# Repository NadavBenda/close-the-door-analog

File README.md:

# Close-the-Door Analog Reminder 🚪🔊

A small battery-powered analog reminder circuit for a shared-house door.

If the door is left open for more than a short delay, the circuit emits a gentle beep sequence as a reminder to close it. The design is intentionally implemented without a microcontroller, using discrete analog/timing logic.

## Motivation

This project started from a real everyday problem: people passing through a shared hallway door often leave it open. Instead of using a software-heavy smart-home solution, the goal was to build a small, manufacturable analog PCB and practice the full hardware design flow independently.

## Design Goals

* Fully analog / no MCU
* Battery powered
* Low standby current
* Reed-switch door sensing
* Gentle, non-intrusive acoustic reminder
* Simple PCB suitable for low-cost fabrication and assembly
* Designed as a first independent end-to-end PCB project

## System Overview

The circuit consists of:

* Reed switch for door-state detection
* CMOS timer logic for delay and beep timing
* Logic gates for signal conditioning
* Passive piezo transducer for the sound output
* Coin-cell battery supply
* Test points for bring-up and debugging

Basic behavior:

```text
Door opens
→ delay timer starts
→ if condition is met
→ short beep sequence
→ silence
```

## Hardware

The board was designed in KiCad and sent to fabrication through JLCPCB.

Main design considerations included:

* Low standby current
* Mechanical placement of reed switch and magnet
* Decoupling for CMOS timing ICs
* Passive piezo drive
* Testability during bring-up
* Manufacturable footprints and BOM preparation

## Status

Assembled

## Known Limitations 

Capacitor Discharge Time: Because the timing circuit is purely analog, the timing capacitor requires a brief period to discharge fully after the door is closed. If the door is cycled (opened and closed) in very rapid succession, the capacitor may remain partially charged, causing the subsequent alarm delay to trigger sooner than the configured duration.

## License

This project is shared for learning and reference

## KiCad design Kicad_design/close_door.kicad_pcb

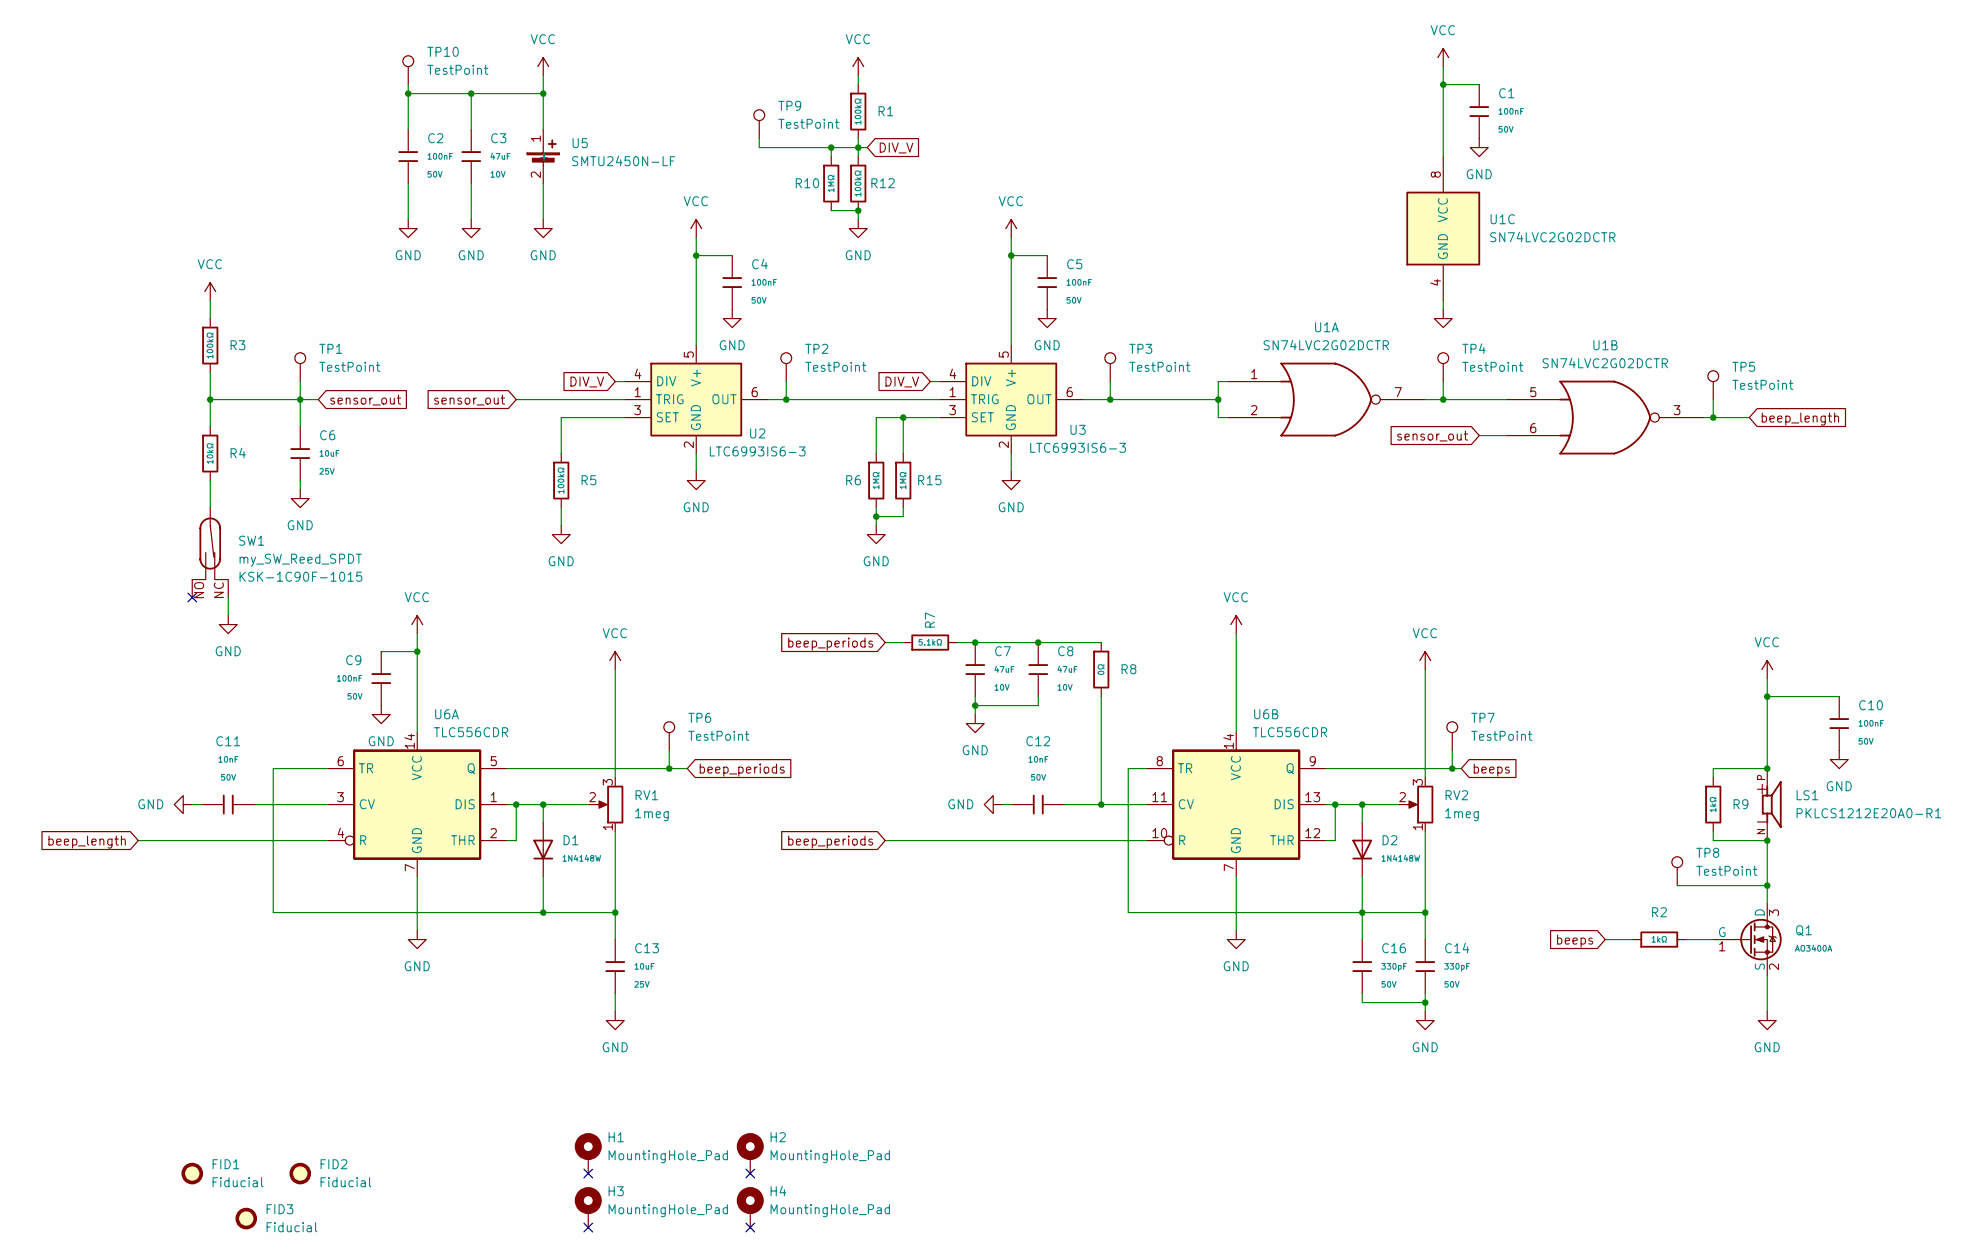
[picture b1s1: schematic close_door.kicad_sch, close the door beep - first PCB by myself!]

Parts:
C1, C2, C4, C5, C9, C10: 100nF; C_0805_2012Metric; Voltage Rated 50V; Tolerance ±10%; Part CC0805KRX7R9BB104; LCSC C49678
C3, C7, C8: 47uF; C_1206_3216Metric; Voltage Rated 10V; Tolerance ±20%; Part CL31A476MPHNNNE; LCSC C96123
C6, C13: 10uF; C_0805_2012Metric; Voltage Rated 25V; Tolerance ±10%; Part CL21A106KAYNNNE; LCSC C15850
C11, C12: 10nF; C_0805_2012Metric; Voltage Rated 50V; Tolerance ±10%; Part CL21B103KBANNNC; LCSC C1710
C14, C16: 330pF; C_0603_1608Metric; Voltage Rated 50V; Tolerance ±5%; Part CL10C331JB8NNNC; LCSC C1664
D1, D2: 1N4148W; D_SOD-123; Forward Voltage (Vf@If) 1V@50mA; Reverse Voltage (Vr) 75V; Part 1N4148W; LCSC C81598
FID1, FID2, FID3: Fiducial; Fiducial_1mm_Mask2mm_with_keepout
H1, H2, H3, H4: MountingHole_Pad; MountingHole_3.2mm_M3_Pad
LS1: PKLCS1212E20A0-R1; PARTREV January 22, 2018
Q1: AO3400A; SOT-23; Part AO3400A; LCSC C20917
R1, R3, R5, R12: 100kΩ; R_0805_2012Metric; Overload Voltage (Max) 150V; Tolerance ±1%; Part 0805W8F1003T5E; LCSC C149504
R2, R9: 1kΩ; R_0805_2012Metric; Overload Voltage (Max) 150V; Tolerance ±1%; Part 0805W8F1001T5E; LCSC C17513
R4: 10kΩ; R_0805_2012Metric; Overload Voltage (Max) 150V; Tolerance ±1%; Part 0805W8F1002T5E; LCSC C17414
R6, R10, R15: 1MΩ; R_0805_2012Metric; Overload Voltage (Max) 150V; Tolerance ±1%; Part 0805W8F1004T5E; LCSC C17514
R7: 5.1kΩ; R_0805_2012Metric; Overload Voltage (Max) 150V; Tolerance ±1%; Part 0805W8F5101T5E; LCSC C27834
R8: 0Ω; R_0805_2012Metric; Overload Voltage (Max) 150V; Tolerance ±1%; Part 0805W8F0000T5E; LCSC C17477
RV1, RV2: 1meg; Potentiometer_Bourns_3296W_Vertical; MPN 3296W-1-105LF; LCSC C83687
SW1: my_SW_Reed_SPDT; KSK-1C90F-1015; MPN KSK-1C90F-1015
TP1, TP2, TP3, TP4, TP5, TP6, TP7, TP8, TP9, TP10: TestPoint; TestPoint_Pad_D1.5mm
U1: SN74LVC2G02DCTR; SOP65P400X130-8N; MPN SN74LVC2G02DCTR; LCSC C94600
U2, U3: LTC6993IS6-3; TSOT-23-6; MPN LTC6993IS6-3#TRMPBF
U5: SMTU2450N-LF; SMTU2450N1LF; Mouser Part Number 614-SMTU2450N-LF.TR
U6: TLC556CDR; SOIC-14_3.9x8.7mm_P1.27mm; MPN TLC556CDR; LCSC C201587

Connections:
DIV_V: R1.2, R10.1, R12.1, TP9.1, U2.4 (DIV), U3.4 (DIV)
GND: C1.2, C2.2, C3.2, C4.2, C5.2, C6.2, C7.2, C8.2, C9.2, C10.2, C11.1, C12.1, C13.2, C14.2, C16.2, Q1.2 (S), R5.2, R6.2, R10.2, R12.2, R15.2, SW1.1, U1.4 (GND), U2.2 (GND), U3.2 (GND), U5.2 (-), U6.7 (GND)
unnamed: C7.1, C8.1, R7.2, R8.1
unnamed: LS1.N, Q1.3 (D), R9.2, TP8.1
unnamed: Q1.1 (G), R2.2
unnamed: R4.2, SW1.2
unnamed: TP4.1, U1.5, U1.7
unnamed: TP2.1, U2.6 (OUT), U3.1 (TRIG)
unnamed: R5.1, U2.3 (SET)
unnamed: TP3.1, U1.1, U1.2, U3.6 (OUT)
unnamed: R6.1, R15.1, U3.3 (SET)
unnamed: C11.2, U6.3 (CV)
unnamed: D1.2, RV1.2, U6.1 (DIS), U6.2 (THR)
unnamed: C13.1, D1.1, RV1.1, U6.6 (TR)
unnamed: C12.2, R8.2, U6.11 (CV)
unnamed: D2.2, RV2.2, U6.12 (THR), U6.13 (DIS)
unnamed: C14.1, C16.1, D2.1, RV2.1, U6.8 (TR)
VCC: C1.1, C2.1, C3.1, C4.1, C5.1, C9.1, C10.1, LS1.P, R1.1, R3.1, R9.1, RV1.3, RV2.3, TP10.1, U1.8 (VCC), U2.5 (V+), U3.5 (V+), U5.1 (+), U6.14 (VCC)
beep_length: TP5.1, U1.3, U6.4 (R)
beep_periods: R7.1, TP6.1, U6.5 (Q), U6.10 (R)
beeps: R2.1, TP7.1, U6.9 (Q)
sensor_out: C6.1, R3.2, R4.1, TP1.1, U1.6, U2.1 (TRIG)

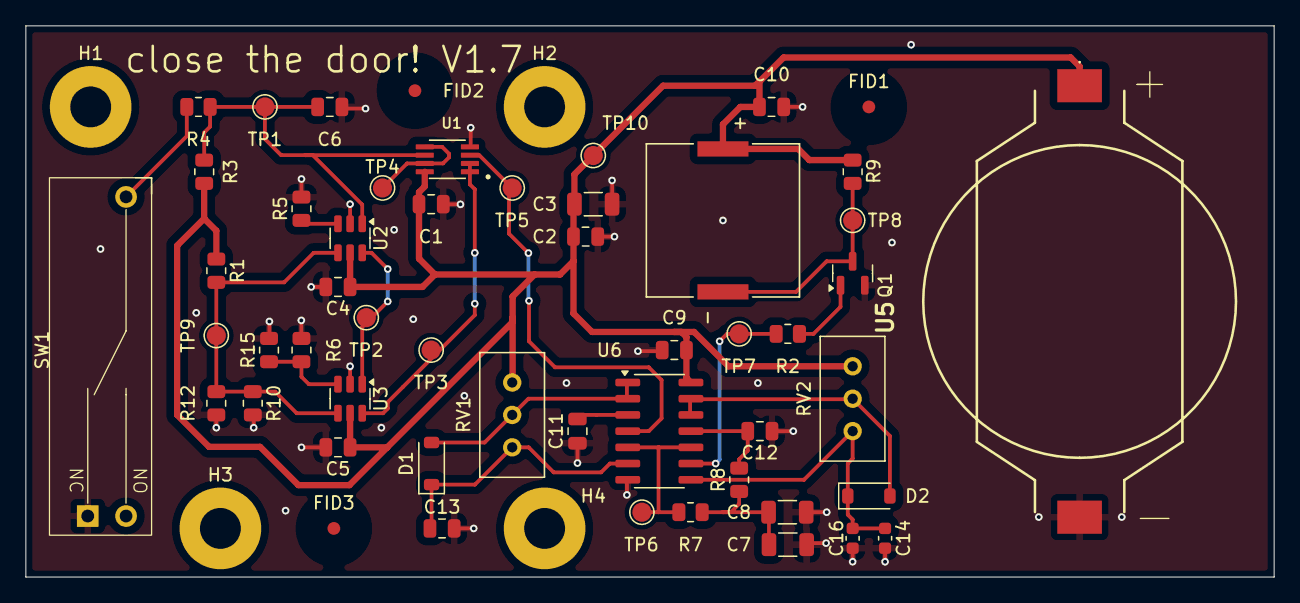
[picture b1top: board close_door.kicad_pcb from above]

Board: 2 copper layers, 97.8 x 43.2 mm, 56 parts (0 on the bottom side), 22 nets.

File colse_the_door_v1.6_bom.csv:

Designator,Footprint,Quantity,Value,LCSC Part #
"C1, C10, C2, C4, C5, C9",0805,6,100nF,C49678
"C11, C12",0805,2,10nF,C1710
"C13, C6",0805,2,10uF,C15850
"C14, C16",C_0603,2,330pF,C1664
"C3, C7, C8",1206,3,47uF,C96123
"D1, D2",D_SOD-123,2,1N4148W,C81598
LS1,PKLCS1212E20A0-R1,1,PKLCS1212E20A0-R1,PKLCS1212E20A0-R1
Q1,Q_SOT-23,1,AO3400A,C20917
"R1, R12, R3, R5",0805,4,100kΩ,C149504
"R10, R15, R6",0805,3,1MΩ,C17514
"R2, R9",R_0805,2,1kΩ,C17513
R4,0805,1,10kΩ,C17414
R7,0805,1,5.1kΩ,C27834
R8,0805,1,0Ω,C17477
"RV1, RV2",Potentiometer_Bourns_3296W_Vertical,2,1meg,C83687
SW1,KSK-1C90F-1015,1,my_SW_Reed_SPDT,KSK-1C90F-1015 
"TP1, TP10, TP2, TP3, TP4, TP5, TP6, TP7, TP8, TP9",TestPoint_Pad_D1.5mm,10,TestPoint,
U1,SOP65P400X130-8N,1,SN74LVC2G02DCTR,C94600
"U2, U3",TSOT-23-6,2,LTC6993IS6-3,LTC6993IS6-3#TRMPBF
U5,BatteryHolder_Renata_SMTU2032-LF_1x2032,1,SMTU2450N-LF,C5443913
U6,SOIC-14_3.9x8.7mm_P1.27mm,1,TLC556CDR,TLC556CDR

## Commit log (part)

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2026-06-29 Update README with PCB image and formatting
    Added an image of the PCB design and reformatted the README for better clarity.
2026-06-29 Organize project files
